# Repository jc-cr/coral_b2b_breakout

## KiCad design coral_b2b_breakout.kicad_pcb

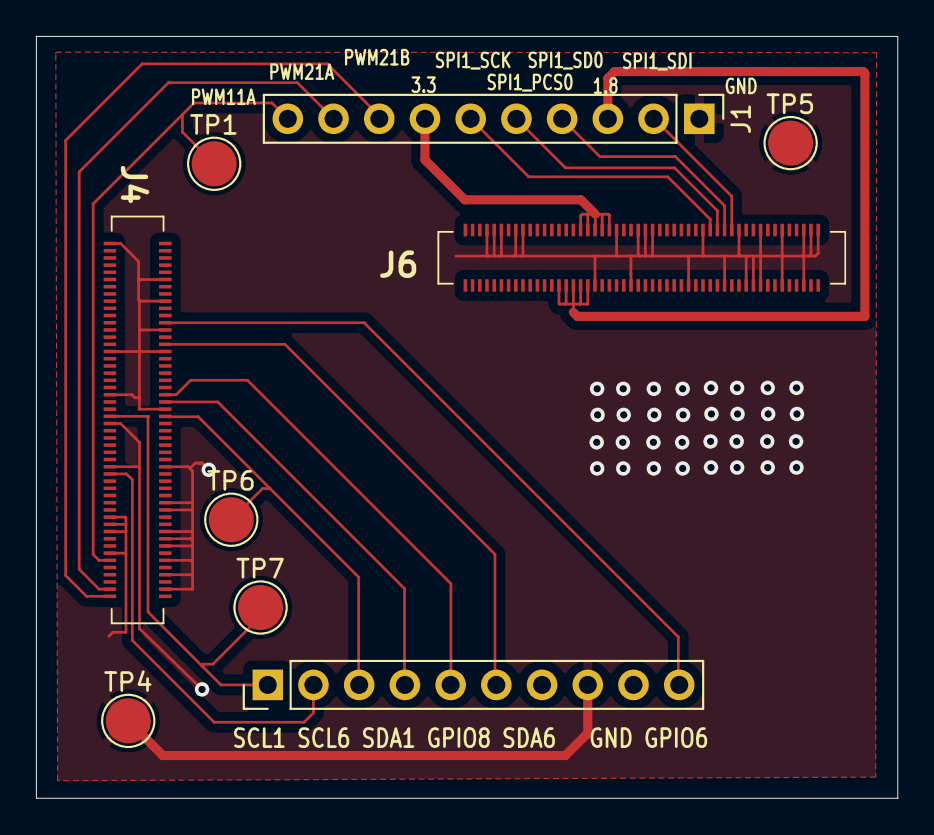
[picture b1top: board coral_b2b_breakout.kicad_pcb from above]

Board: 2 copper layers, 47.8 x 42.3 mm, 9 parts (0 on the bottom side), 17 nets.

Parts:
J1, J2: Conn_01x10; PinHeader_1x10_P2.54mm_Vertical
J4, J6: DF40C-100DS-0.4V_51_; DF40C100DS04V51
TP1, TP4, TP5, TP6, TP7: TestPoint; TestPoint_Pad_D2.5mm

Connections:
/Board To Board Conn 1/FLEXPWM1_PWM1_A: J1.10, J4.11, TP1.1
/Board To Board Conn 1/FLEXPWM2_PWM1_A: J1.9, J4.3
/Board To Board Conn 1/FLEXPWM2_PWM1_B: J1.8, J4.1
/Board To Board Conn 1/GPIO_SNVS_04: J2.5, J4.58
/Board To Board Conn 1/GPIO_SNVS_06: J2.10, J4.78
/Board To Board Conn 1/GPIO_SNVS_08: J2.4, J4.56
/Board To Board Conn 1/I2C1_SCL: J2.1, J4.51, TP7.1
/Board To Board Conn 1/I2C1_SDA: J2.3, J4.52, TP6.1
/Board To Board Conn 1/I2C6_SCL: J2.2, J4.35
/Board To Board Conn 1/I2C6_SDA: J2.6, J4.72
/Board To Board Conn 2/+1.8VDC: J1.3, J6.28, J6.30, J6.32, J6.34, J6.36
/Board To Board Conn 2/+3.3VDC: J1.7, J6.33, J6.35, J6.37, J6.39, J6.41
/Board To Board Conn 2/LPSPI1_PCS0: J1.5, J6.71
/Board To Board Conn 2/LPSPI1_SCK: J1.6, J6.69
/Board To Board Conn 2/LPSPI1_SDI: J1.2, J6.75
/Board To Board Conn 2/LPSPI1_SDO: J1.4, J6.73
GND: J1.1, J2.8, J4.4, J4.8, J4.12, J4.13, J4.16, J4.18, J4.19, J4.20, J4.21, J4.23, J4.26, J4.28, J4.37, J4.38, J4.49, J4.54, J4.57, J4.69, J4.70, J4.76, J4.84, J4.90, J4.99, J6.7, J6.9, J6.11, J6.15, J6.17, J6.38, J6.43, J6.48, J6.49, J6.51, J6.53, J6.64, J6.67, J6.74, J6.77, J6.80, J6.82, J6.83, J6.84, J6.89, J6.90, J6.95, J6.96, J6.97, J6.99, TP4.1, TP5.1

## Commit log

2024-06-18 PCB rev 0.0.0
